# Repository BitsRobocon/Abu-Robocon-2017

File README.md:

# Abu-Robocon-2017

This Repository contains only the CAD models prepared for the Abu-Robocon competition of 2017

## Official Website With Rule Book

https://aburobocon.net/

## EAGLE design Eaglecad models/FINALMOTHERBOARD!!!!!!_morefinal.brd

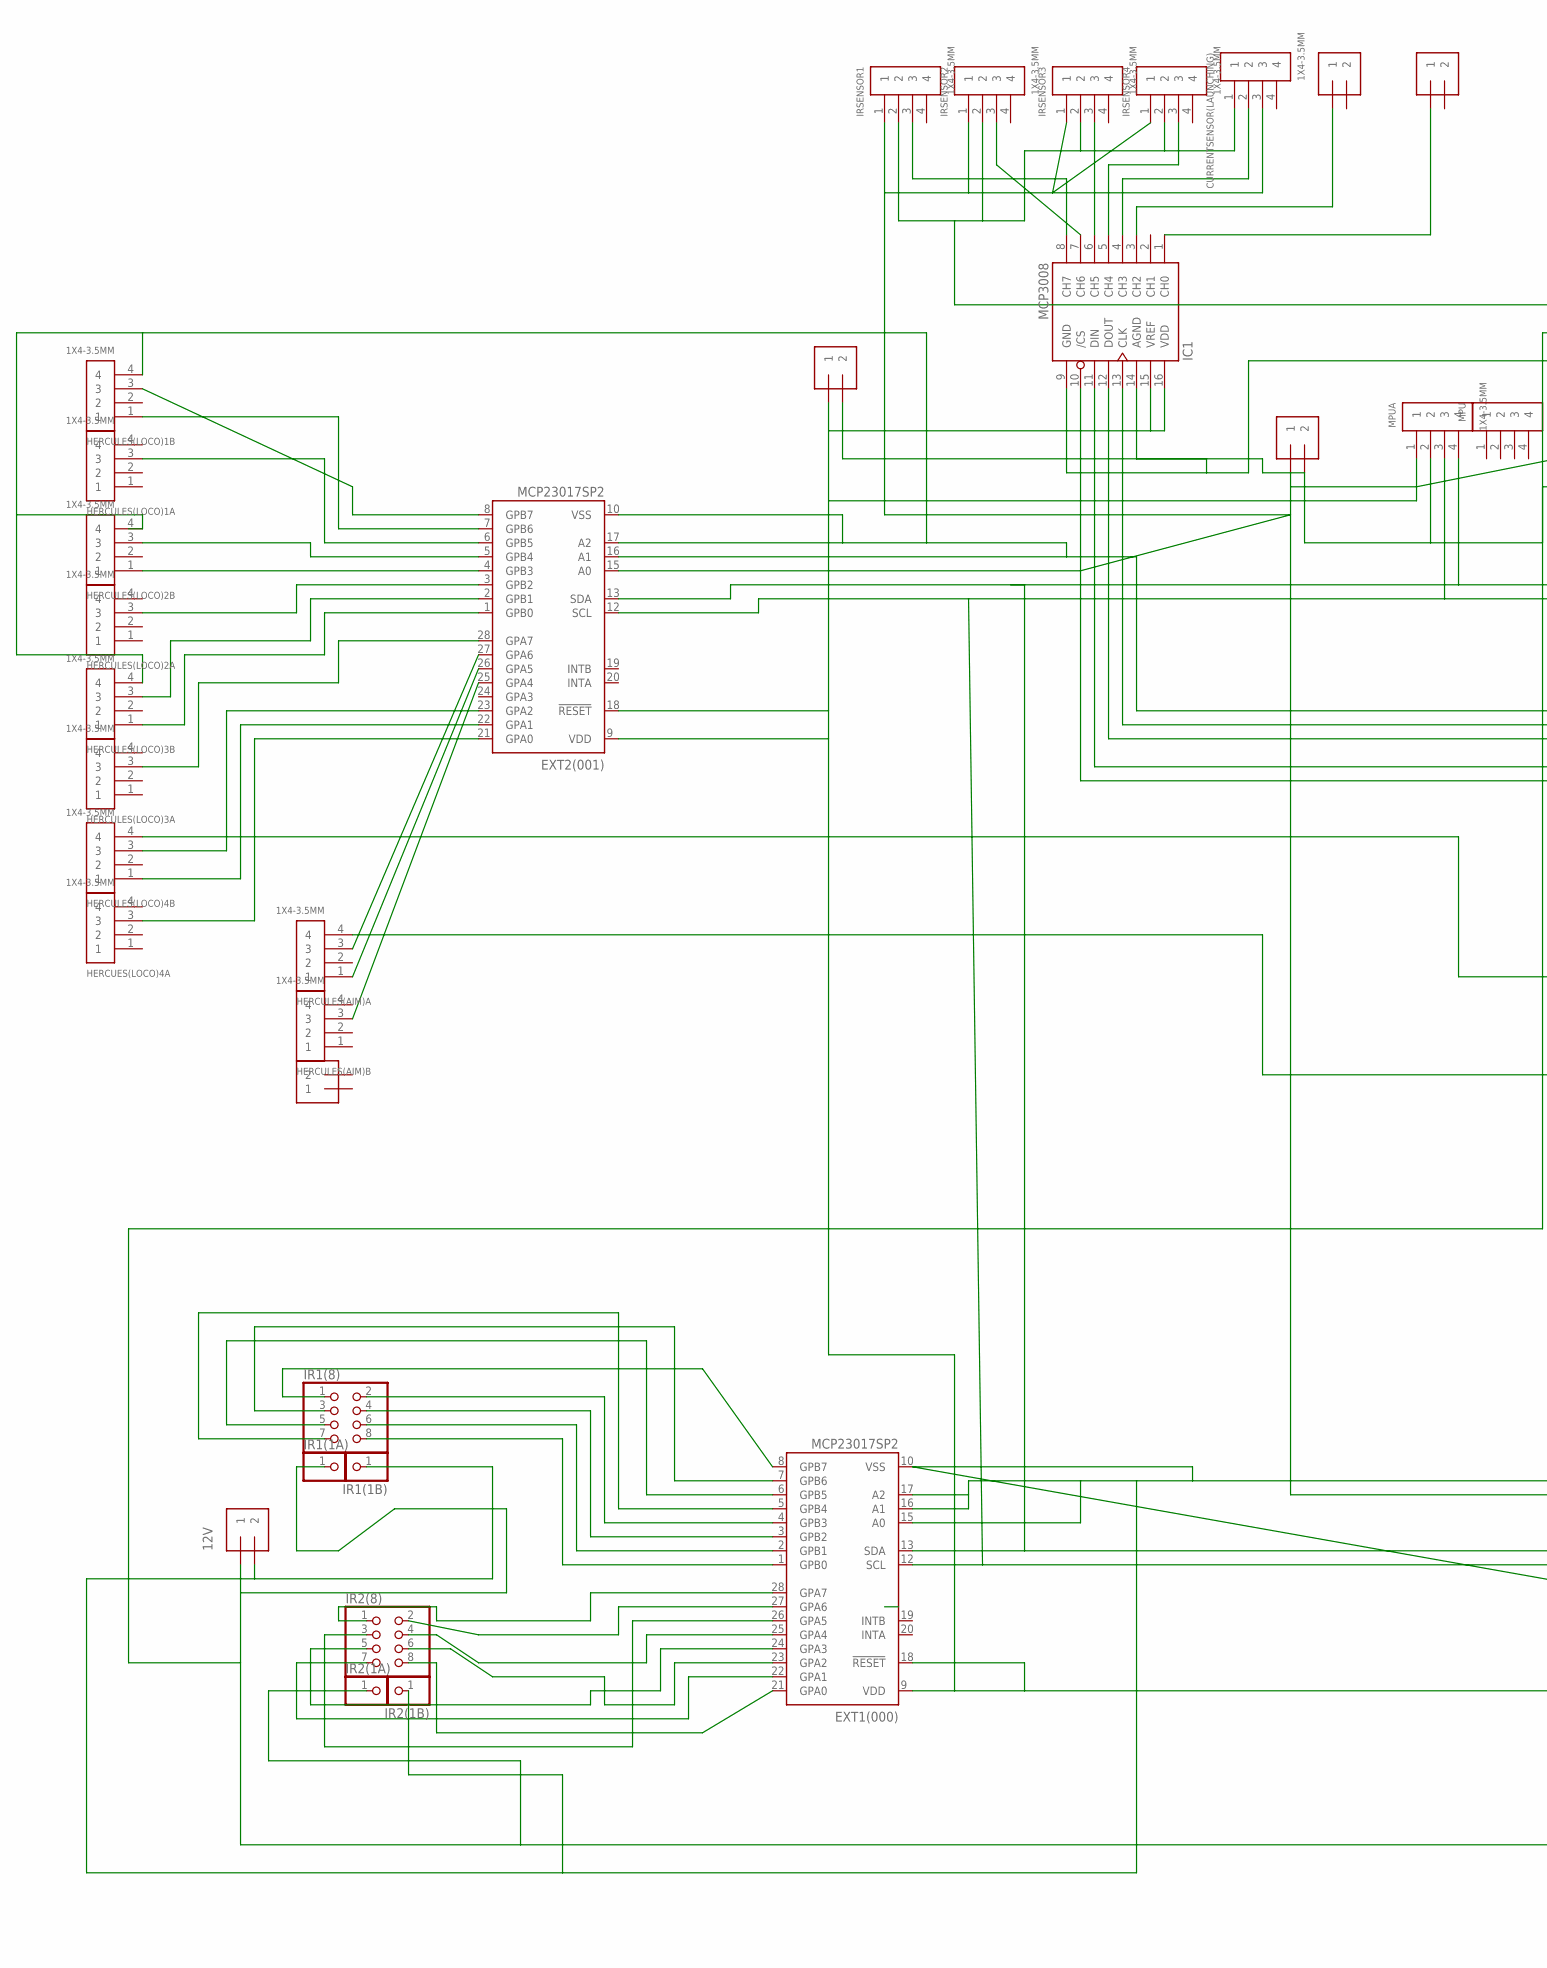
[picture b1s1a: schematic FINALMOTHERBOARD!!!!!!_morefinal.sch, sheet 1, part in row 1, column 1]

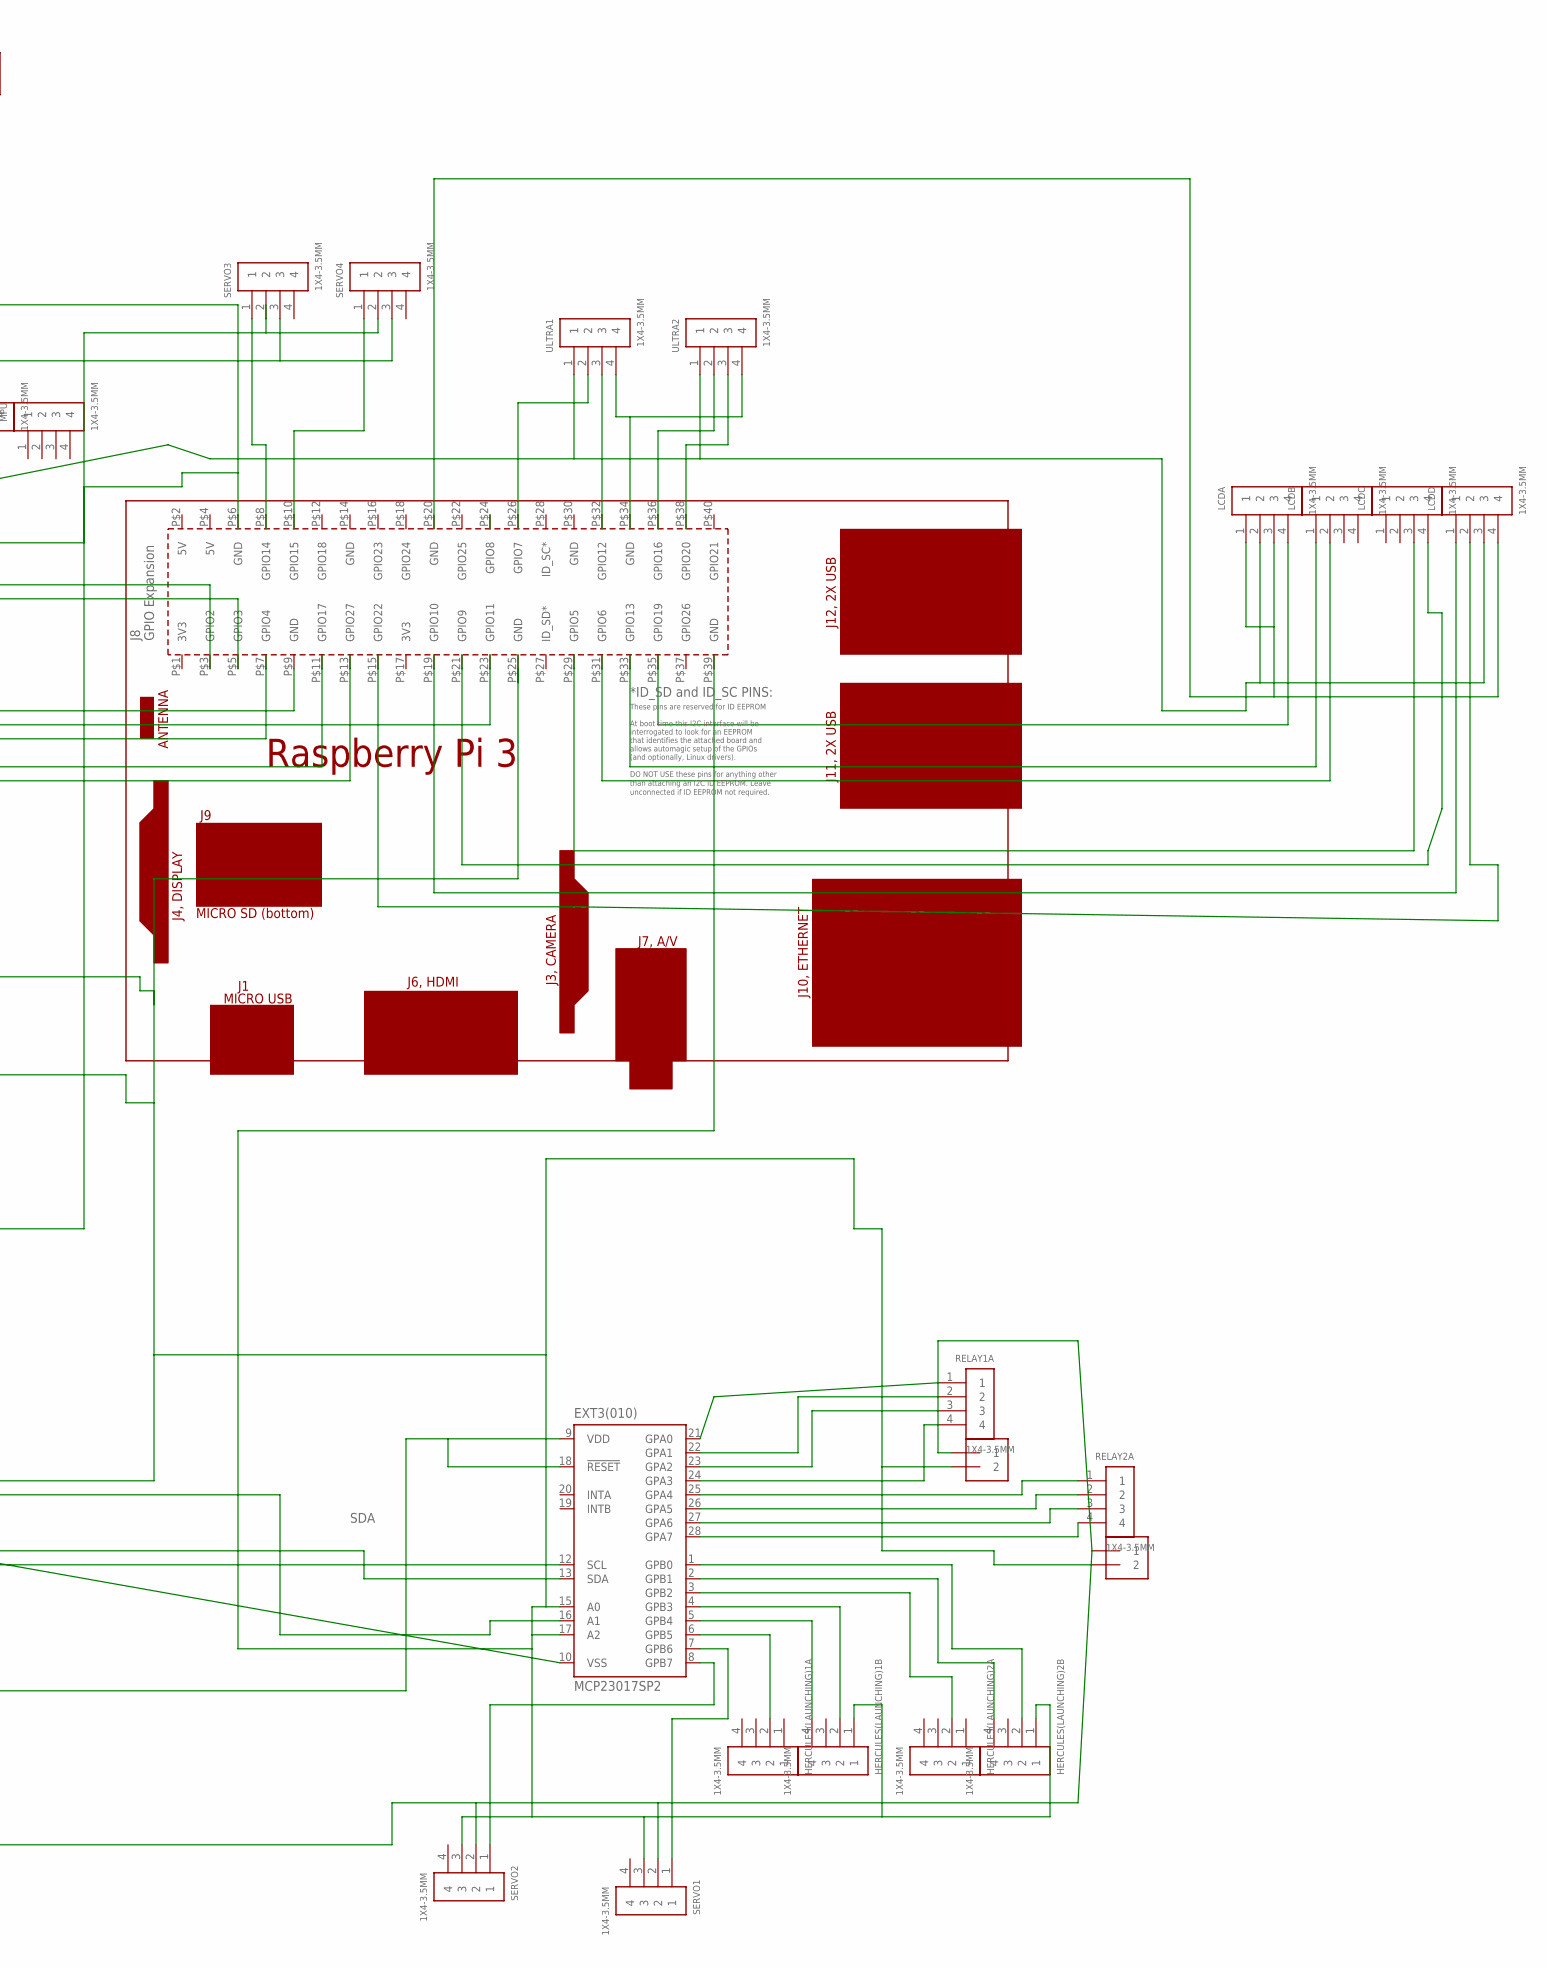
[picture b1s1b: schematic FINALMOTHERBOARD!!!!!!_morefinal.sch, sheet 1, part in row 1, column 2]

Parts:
3.3V, 5V, 12V: 1X2-3.5MM
CURRENTSENSOR(LAUNCHING): 1X4-3.5MM; 1X04-3.5MM
EXT1(000), EXT2(001), EXT3(010): MCP23017SP2; DIL28-3-ROUND
HERCUES(LOCO)4A: 1X4-3.5MM; 1X04-3.5MM
HERCULES(AIM)A: 1X4-3.5MM; 1X04-3.5MM
HERCULES(AIM)B: 1X4-3.5MM; 1X04-3.5MM
HERCULES(AIM)C: 1X2-3.5MM
HERCULES(LAUNCHING)1A, HERCULES(LAUNCHING)1B, HERCULES(LAUNCHING)2A, HERCULES(LAUNCHING)2B: 1X4-3.5MM; 1X04-3.5MM
HERCULES(LOCO)1A, HERCULES(LOCO)1B, HERCULES(LOCO)2A, HERCULES(LOCO)2B, HERCULES(LOCO)3A, HERCULES(LOCO)3B, HERCULES(LOCO)4B: 1X4-3.5MM; 1X04-3.5MM
IC1: MCP3008; DIL16
IR1(1A), IR1(1B), IR2(1A), IR2(1B): PINHD-1X1; 1X01
IR1(8), IR2(8): PINHD-2X4; 2X04
IR(LOCO)1ANALOG, IR(LOCO)2ANALOG: 1X2-3.5MM
IRSENSOR1, IRSENSOR2, IRSENSOR3, IRSENSOR4: 1X4-3.5MM; 1X04-3.5MM
LCDA: 1X4-3.5MM; 1X04-3.5MM
LCDB: 1X4-3.5MM; 1X04-3.5MM
LCDC: 1X4-3.5MM; 1X04-3.5MM
LCDD: 1X4-3.5MM; 1X04-3.5MM
MPU: 1X4-3.5MM; 1X04-3.5MM
MPUA: 1X4-3.5MM; 1X04-3.5MM
PCB1: RPI3
RELAY1A, RELAY2A: 1X4-3.5MM; 1X04-3.5MM
RELAY1B, RELAY2B: 1X2-3.5MM
SERVO1, SERVO2, SERVO3, SERVO4: 1X4-3.5MM; 1X04-3.5MM
ULTRA1, ULTRA2: 1X4-3.5MM; 1X04-3.5MM

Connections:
3.3V: 3.3V.1, EXT1(000).9 (VDD), EXT1(000).18 (!RESET), EXT2(001).9 (VDD), EXT2(001).18 (!RESET), EXT3(010).9 (VDD), EXT3(010).18 (!RESET), IC1.15 (VREF), IC1.16 (VDD), MPUA.1
5V: 5V.1, CURRENTSENSOR(LAUNCHING).3, EXT2(001).15 (A0), EXT3(010).16 (A1), IRSENSOR1.1, IRSENSOR2.1, IRSENSOR3.1, IRSENSOR4.1, LCDA.2, LCDD.3, ULTRA1.1, ULTRA2.1
12V: 12V.1, IR1(1A).1, IR2(1A).1, RELAY1B.1, RELAY2B.1, SERVO1.2, SERVO2.2, SERVO3.2, SERVO4.2
ANALOG(CURRENTSENSOR): CURRENTSENSOR(LAUNCHING).2, IC1.4 (CH3)
ANALOG(IR1): IC1.8 (CH7), IRSENSOR1.3
ANALOG(IR2): IC1.7 (CH6), IRSENSOR2.3
CS(ADC): IC1.10 (/CS), PCB1.P$13 (GPIO27)
CS(MCP3008): PCB1.P$24 (GPIO8)
DIN(MCP3008): IC1.11 (DIN), PCB1.P$11 (GPIO17)
DIR1(HERC1L): EXT2(001).8 (GPB7), HERCULES(LOCO)1B.3
DIR1(HERCULES2)LOCO: EXT2(001).5 (GPB4), HERCULES(LOCO)2B.3
DIR1(HERCULES3)LOCO: EXT2(001).2 (GPB1), HERCULES(LOCO)3B.3
DIR1(HERCULES4)LOCO: EXT2(001).23 (GPA2), HERCULES(LOCO)4B.3
DIR2(HERCULES1)LOCO: EXT2(001).6 (GPB5), HERCULES(LOCO)1A.3
DIR2(HERCULES2)LOCO: EXT2(001).3 (GPB2), HERCULES(LOCO)2A.3
DIR2(HERCULES3)LOCO: EXT2(001).28 (GPA7), HERCULES(LOCO)3A.3
DIR2(HERCULES4)LOCO: EXT2(001).21 (GPA0), HERCUES(LOCO)4A.3
DOUT(MCP3008): IC1.12 (DOUT), PCB1.P$7 (GPIO4)
ECHO(US1: PCB1.P$32 (GPIO12), ULTRA1.3
ECHO(US2): PCB1.P$38 (GPIO20), ULTRA2.3
ENABLE(LCD): LCDB.2, PCB1.P$31 (GPIO6)
GND: 12V.2, EXT1(000).10 (VSS), EXT1(000).15 (A0), EXT1(000).16 (A1), EXT1(000).17 (A2), EXT3(010).10 (VSS), EXT3(010).15 (A0), EXT3(010).17 (A2), HERCULES(AIM)A.4, HERCULES(LAUNCHING)1B.1, HERCULES(LAUNCHING)2B.1, HERCULES(LOCO)4B.4, IR1(1B).1, IR2(1B).1, PCB1.P$25 (GND), RELAY1B.2, RELAY2B.2, SERVO1.3, SERVO2.3
GND6: EXT2(001).10 (VSS), EXT2(001).16 (A1), EXT2(001).17 (A2), HERCULES(LOCO)1B.4, HERCULES(LOCO)2B.4, HERCULES(LOCO)3B.4, PCB1.P$9 (GND)
GND8: PCB1.P$34 (GND), ULTRA1.4, ULTRA2.4
GND9: 3.3V.2, 5V.2, CURRENTSENSOR(LAUNCHING).1, IC1.9 (GND), IC1.14 (AGND), IRSENSOR1.2, IRSENSOR2.2, IRSENSOR3.2, IRSENSOR4.2, MPUA.2, PCB1.P$6 (GND), SERVO3.3, SERVO4.3
GRND1: LCDA.1, LCDA.3, LCDD.4
HERCULES(AIM)DIR1: EXT2(001).27 (GPA6), HERCULES(AIM)A.3
HERCULES(AIM)DIR2: EXT2(001).25 (GPA4), HERCULES(AIM)B.3
HERCULES(LAUNCHING1)DIR1: EXT3(010).4 (GPB3), HERCULES(LAUNCHING)1B.2
HERCULES(LAUNCHING1)DIR2: EXT3(010).6 (GPB5), HERCULES(LAUNCHING)1A.2
HERCULES(LAUNCHING1)PWM: EXT3(010).5 (GPB4), HERCULES(LAUNCHING)1B.4
HERCULES(LAUNCHING2)DIR1: EXT3(010).1 (GPB0), HERCULES(LAUNCHING)2B.2
HERCULES(LAUNCHING2)DIR2: EXT3(010).3 (GPB2), HERCULES(LAUNCHING)2A.2
HERCULES(LAUNCHING2)PWM: EXT3(010).2 (GPB1), HERCULES(LAUNCHING)2B.4
HERCULES(PWM)DIR1: EXT2(001).26 (GPA5), HERCULES(AIM)A.1
INPUT(SERVO3): PCB1.P$8 (GPIO14), SERVO3.1
INPUT(SERVO4): PCB1.P$10 (GPIO15), SERVO4.1
IR3(ANALOG): IC1.6 (CH5), IRSENSOR3.3
IR4(ANALOG): IC1.5 (CH4), IRSENSOR4.3
IR(JPULSE)1: IC1.3 (CH2), IR(LOCO)1ANALOG.1
IR(JPULSE)2: IC1.1 (CH0), IR(LOCO)2ANALOG.1
LCDD0: LCDD.2, PCB1.P$15 (GPIO22)
LCDD1: LCDD.1, PCB1.P$19 (GPIO10)
LCDD2: LCDC.4, PCB1.P$21 (GPIO9)
LCDD3: LCDC.3, PCB1.P$29 (GPIO5)
unnamed: EXT1(000).6 (GPB5), IR1(8).5
unnamed: EXT1(000).4 (GPB3), IR1(8).2
O1(IR1): EXT1(000).8 (GPB7), IR1(8).1
O1(IR2): EXT1(000).28 (GPA7), IR2(8).1
O2(IR1): EXT1(000).7 (GPB6), IR1(8).3
O2(IR2): EXT1(000).27 (GPA6), IR2(8).2
O3(IR2): EXT1(000).26 (GPA5), IR2(8).3
O4(IR1): EXT1(000).5 (GPB4), IR1(8).7
O4(IR2): EXT1(000).25 (GPA4), IR2(8).4
O5(IR2): EXT1(000).24 (GPA3), IR2(8).5
O6(IR1): EXT1(000).3 (GPB2), IR1(8).4
O6(IR2): EXT1(000).23 (GPA2), IR2(8).6
O7(IR1): EXT1(000).2 (GPB1), IR1(8).6
O7(IR2): EXT1(000).22 (GPA1), IR2(8).7
O8(IR1): EXT1(000).1 (GPB0), IR1(8).8
O8(IR2): EXT1(000).21 (GPA0), IR2(8).8
PWM(HERCULES1)LOCO: EXT2(001).7 (GPB6), HERCULES(LOCO)1B.1
PWM(HERCULES2)LOCO: EXT2(001).4 (GPB3), HERCULES(LOCO)2B.1
PWM(HERCULES3)LOCO: EXT2(001).1 (GPB0), HERCULES(LOCO)3B.1
PWM(HERCULES4)LOCO: EXT2(001).22 (GPA1), HERCULES(LOCO)4B.1
R/W(LCD): LCDB.1, PCB1.P$33 (GPIO13)
REGISTERSELECT(LCD): LCDA.4, PCB1.P$35 (GPIO19)
REL1(STEP1): EXT3(010).21 (GPA0), RELAY1A.1
REL1(STEP2): EXT3(010).25 (GPA4), RELAY2A.1
REL2(STEP1): EXT3(010).22 (GPA1), RELAY1A.2
REL2(STEP2): EXT3(010).26 (GPA5), RELAY2A.2
REL3(STEP1): EXT3(010).23 (GPA2), RELAY1A.3
REL3(STEP2): EXT3(010).27 (GPA6), RELAY2A.3
REL4(STEP1): EXT3(010).24 (GPA3), RELAY1A.4
REL4(STEP2): EXT3(010).28 (GPA7), RELAY2A.4
SCK: IC1.13 (CLK), PCB1.P$23 (GPIO11)
SCL: EXT1(000).12 (SCL), EXT2(001).12 (SCL), EXT3(010).12 (SCL), MPUA.3, PCB1.P$5 (GPIO3)
SDA: EXT1(000).13 (SDA), EXT2(001).13 (SDA), EXT3(010).13 (SDA), MPUA.4, PCB1.P$3 (GPIO2)
SERV01(INPUT): EXT3(010).7 (GPB6), SERVO1.1
SERVO2(INPUT): EXT3(010).8 (GPB7), SERVO2.1
TRIG(US1): PCB1.P$26 (GPIO7), ULTRA1.2
TRIG(US2): PCB1.P$36 (GPIO16), ULTRA2.2

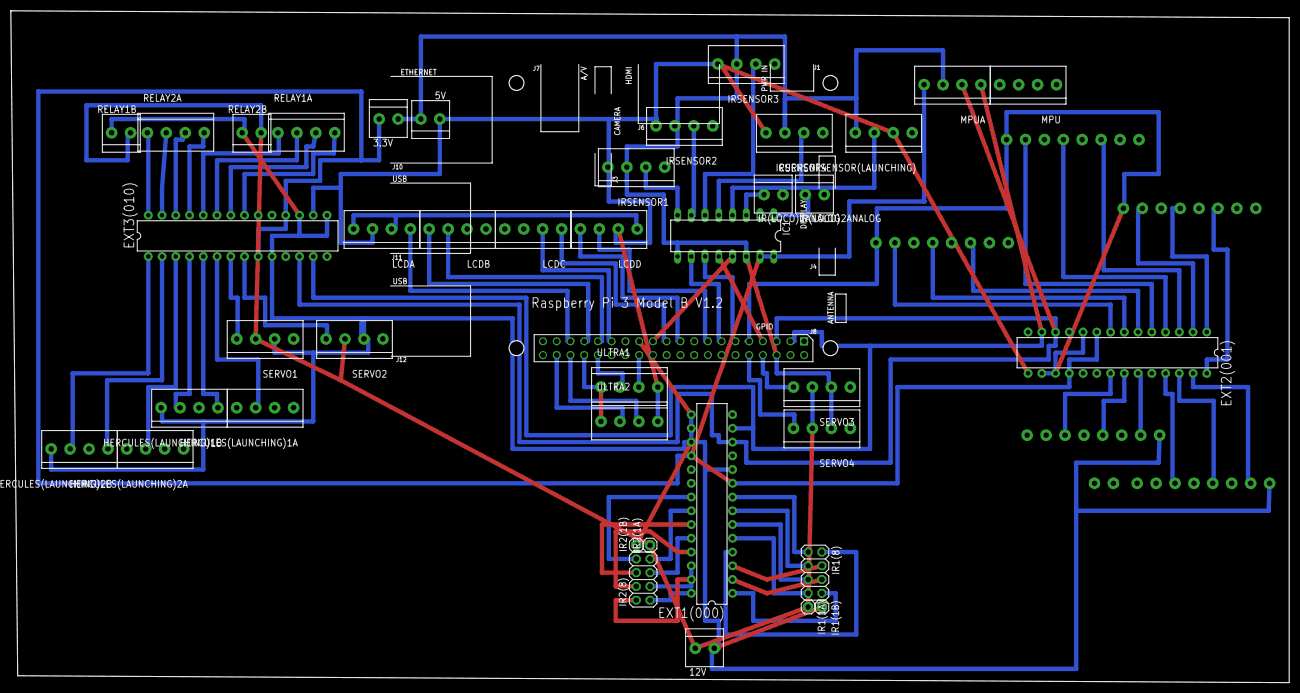
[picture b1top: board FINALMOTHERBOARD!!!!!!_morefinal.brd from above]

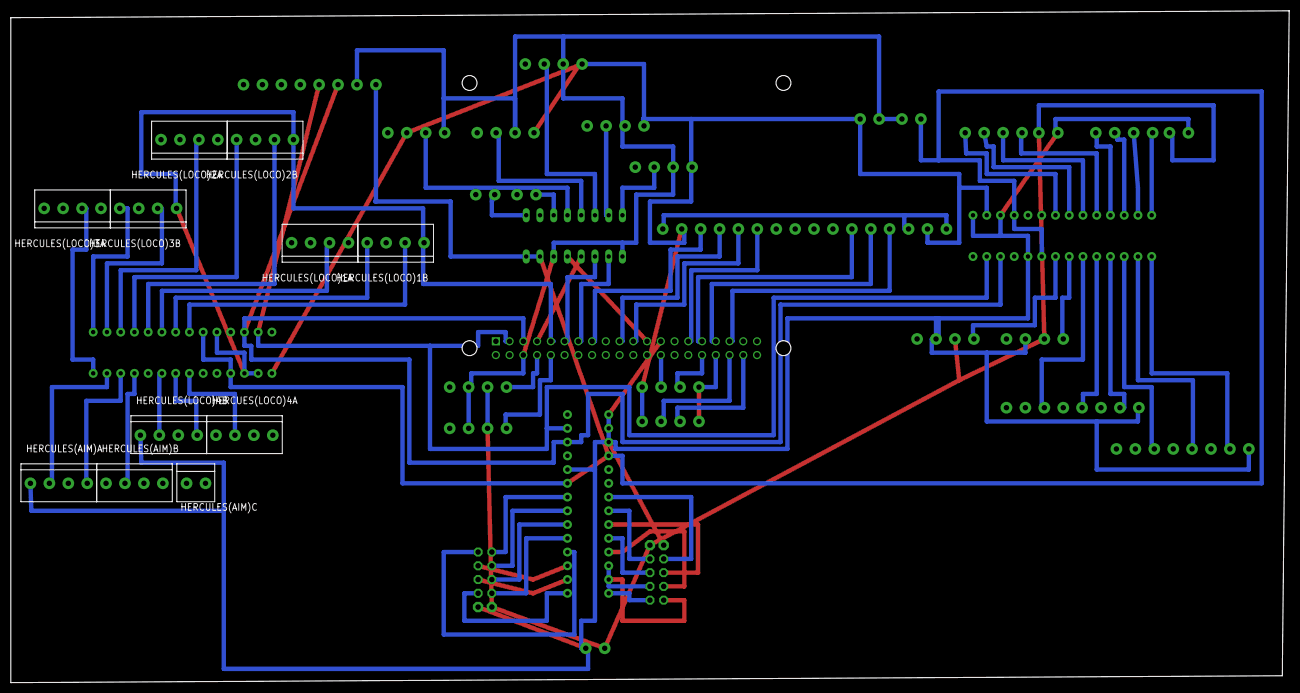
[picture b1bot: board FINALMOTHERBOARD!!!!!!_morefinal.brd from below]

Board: 2 copper layers, 236.2 x 124.1 mm, 52 parts (11 on the bottom side), 81 nets.

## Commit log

2018-12-06 Adding completed files
